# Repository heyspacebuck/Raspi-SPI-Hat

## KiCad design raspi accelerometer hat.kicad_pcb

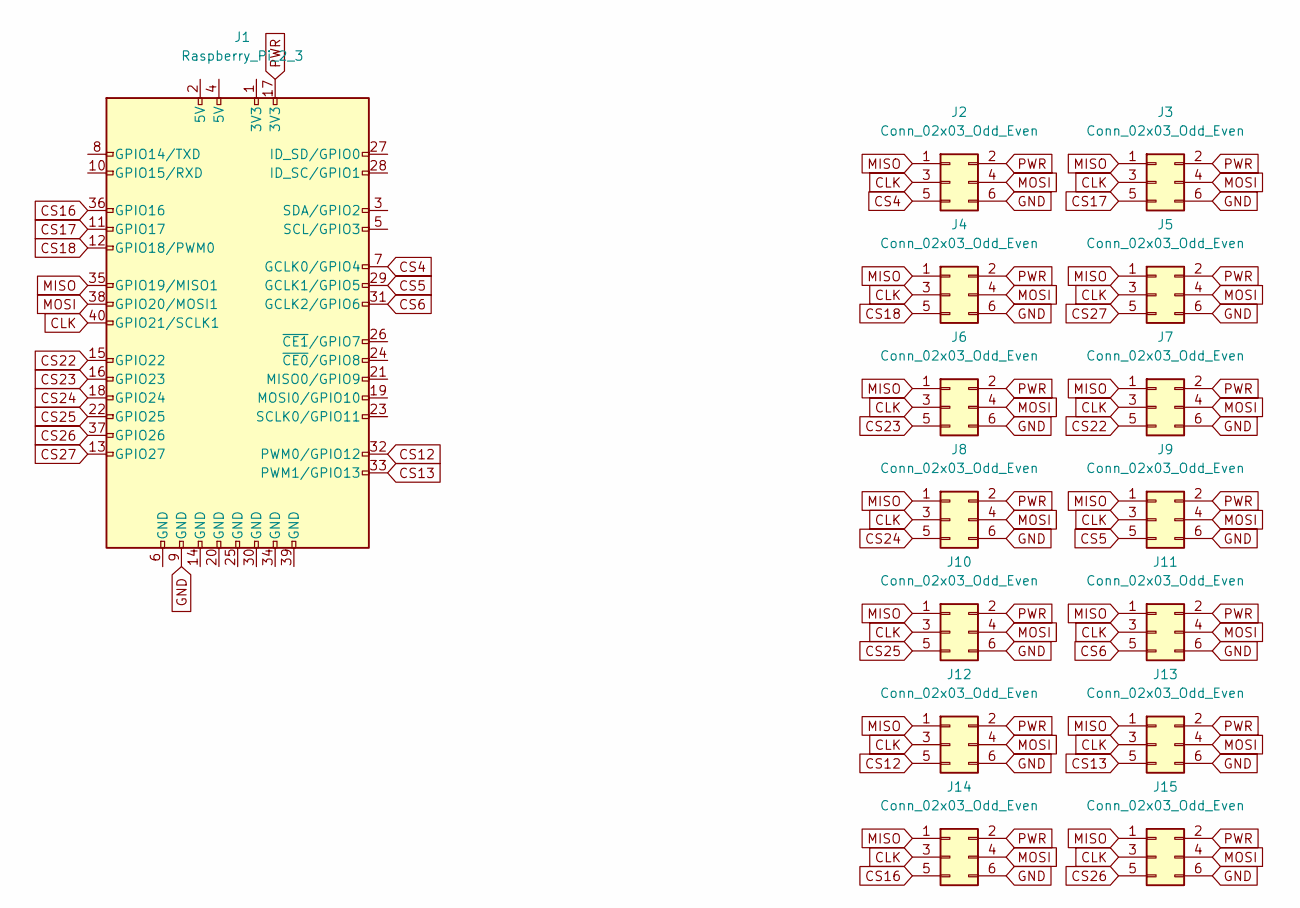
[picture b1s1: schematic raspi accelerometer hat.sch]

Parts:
J1: Raspberry_Pi_2_3; PinSocket_2x20_P2.54mm_Vertical
J2, J3, J4, J5, J6, J7, J8, J9, J10, J11, J12, J13, J14, J15: Conn_02x03_Odd_Even; IDC-Header_2x03_P2.54mm_Vertical

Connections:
CLK: J1.40 (GPIO21/SCLK1), J2.3, J3.3, J4.3, J5.3, J6.3, J7.3, J8.3, J9.3, J10.3, J11.3, J12.3, J13.3, J14.3, J15.3
CS4: J1.7 (GCLK0/GPIO4), J2.5
CS5: J1.29 (GCLK1/GPIO5), J9.5
CS6: J1.31 (GCLK2/GPIO6), J11.5
CS12: J1.32 (PWM0/GPIO12), J12.5
CS13: J1.33 (PWM1/GPIO13), J13.5
CS16: J1.36 (GPIO16), J14.5
CS17: J1.11 (GPIO17), J3.5
CS18: J1.12 (GPIO18/PWM0), J4.5
CS22: J1.15 (GPIO22), J7.5
CS23: J1.16 (GPIO23), J6.5
CS24: J1.18 (GPIO24), J8.5
CS25: J1.22 (GPIO25), J10.5
CS26: J1.37 (GPIO26), J15.5
CS27: J1.13 (GPIO27), J5.5
GND: J1.9 (GND), J2.6, J3.6, J4.6, J5.6, J6.6, J7.6, J8.6, J9.6, J10.6, J11.6, J12.6, J13.6, J14.6, J15.6
MISO: J1.35 (GPIO19/MISO1), J2.1, J3.1, J4.1, J5.1, J6.1, J7.1, J8.1, J9.1, J10.1, J11.1, J12.1, J13.1, J14.1, J15.1
MOSI: J1.38 (GPIO20/MOSI1), J2.4, J3.4, J4.4, J5.4, J6.4, J7.4, J8.4, J9.4, J10.4, J11.4, J12.4, J13.4, J14.4, J15.4
PWR: J1.17 (3V3), J2.2, J3.2, J4.2, J5.2, J6.2, J7.2, J8.2, J9.2, J10.2, J11.2, J12.2, J13.2, J14.2, J15.2

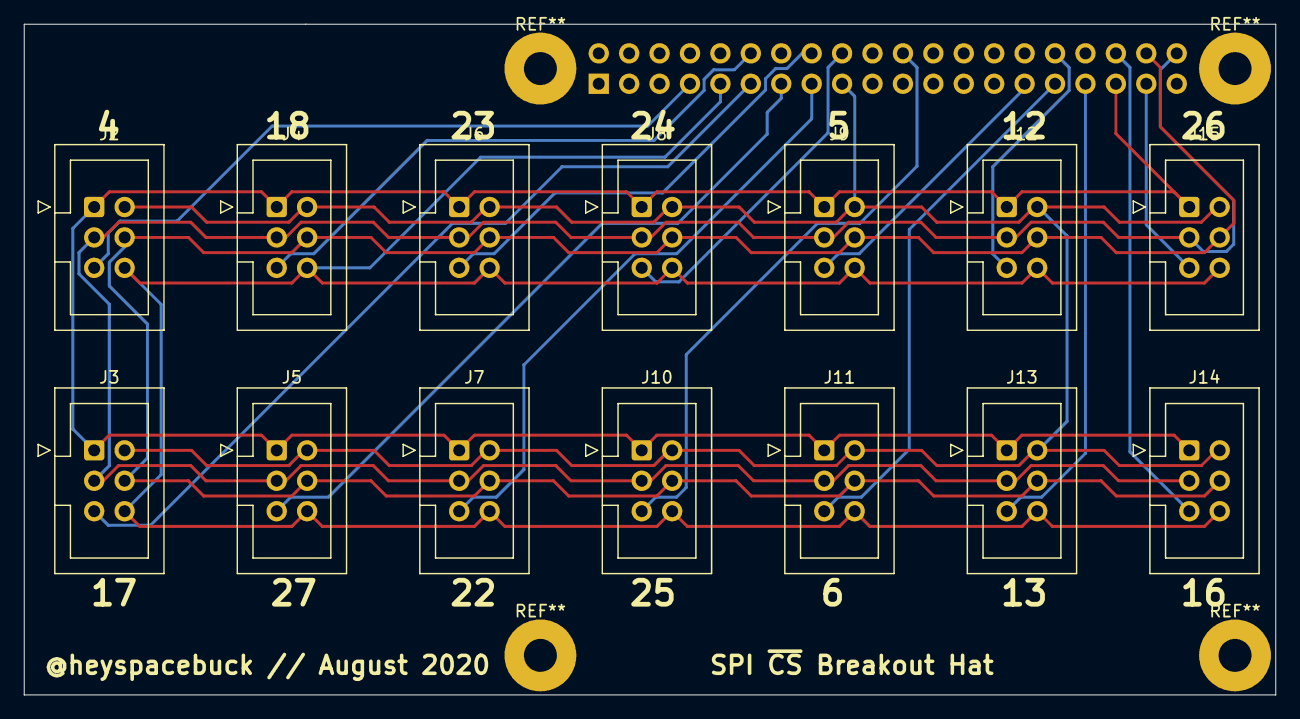
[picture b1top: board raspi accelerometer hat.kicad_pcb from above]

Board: 2 copper layers, 104.5 x 56.0 mm, 15 parts (1 on the bottom side), 19 nets.
